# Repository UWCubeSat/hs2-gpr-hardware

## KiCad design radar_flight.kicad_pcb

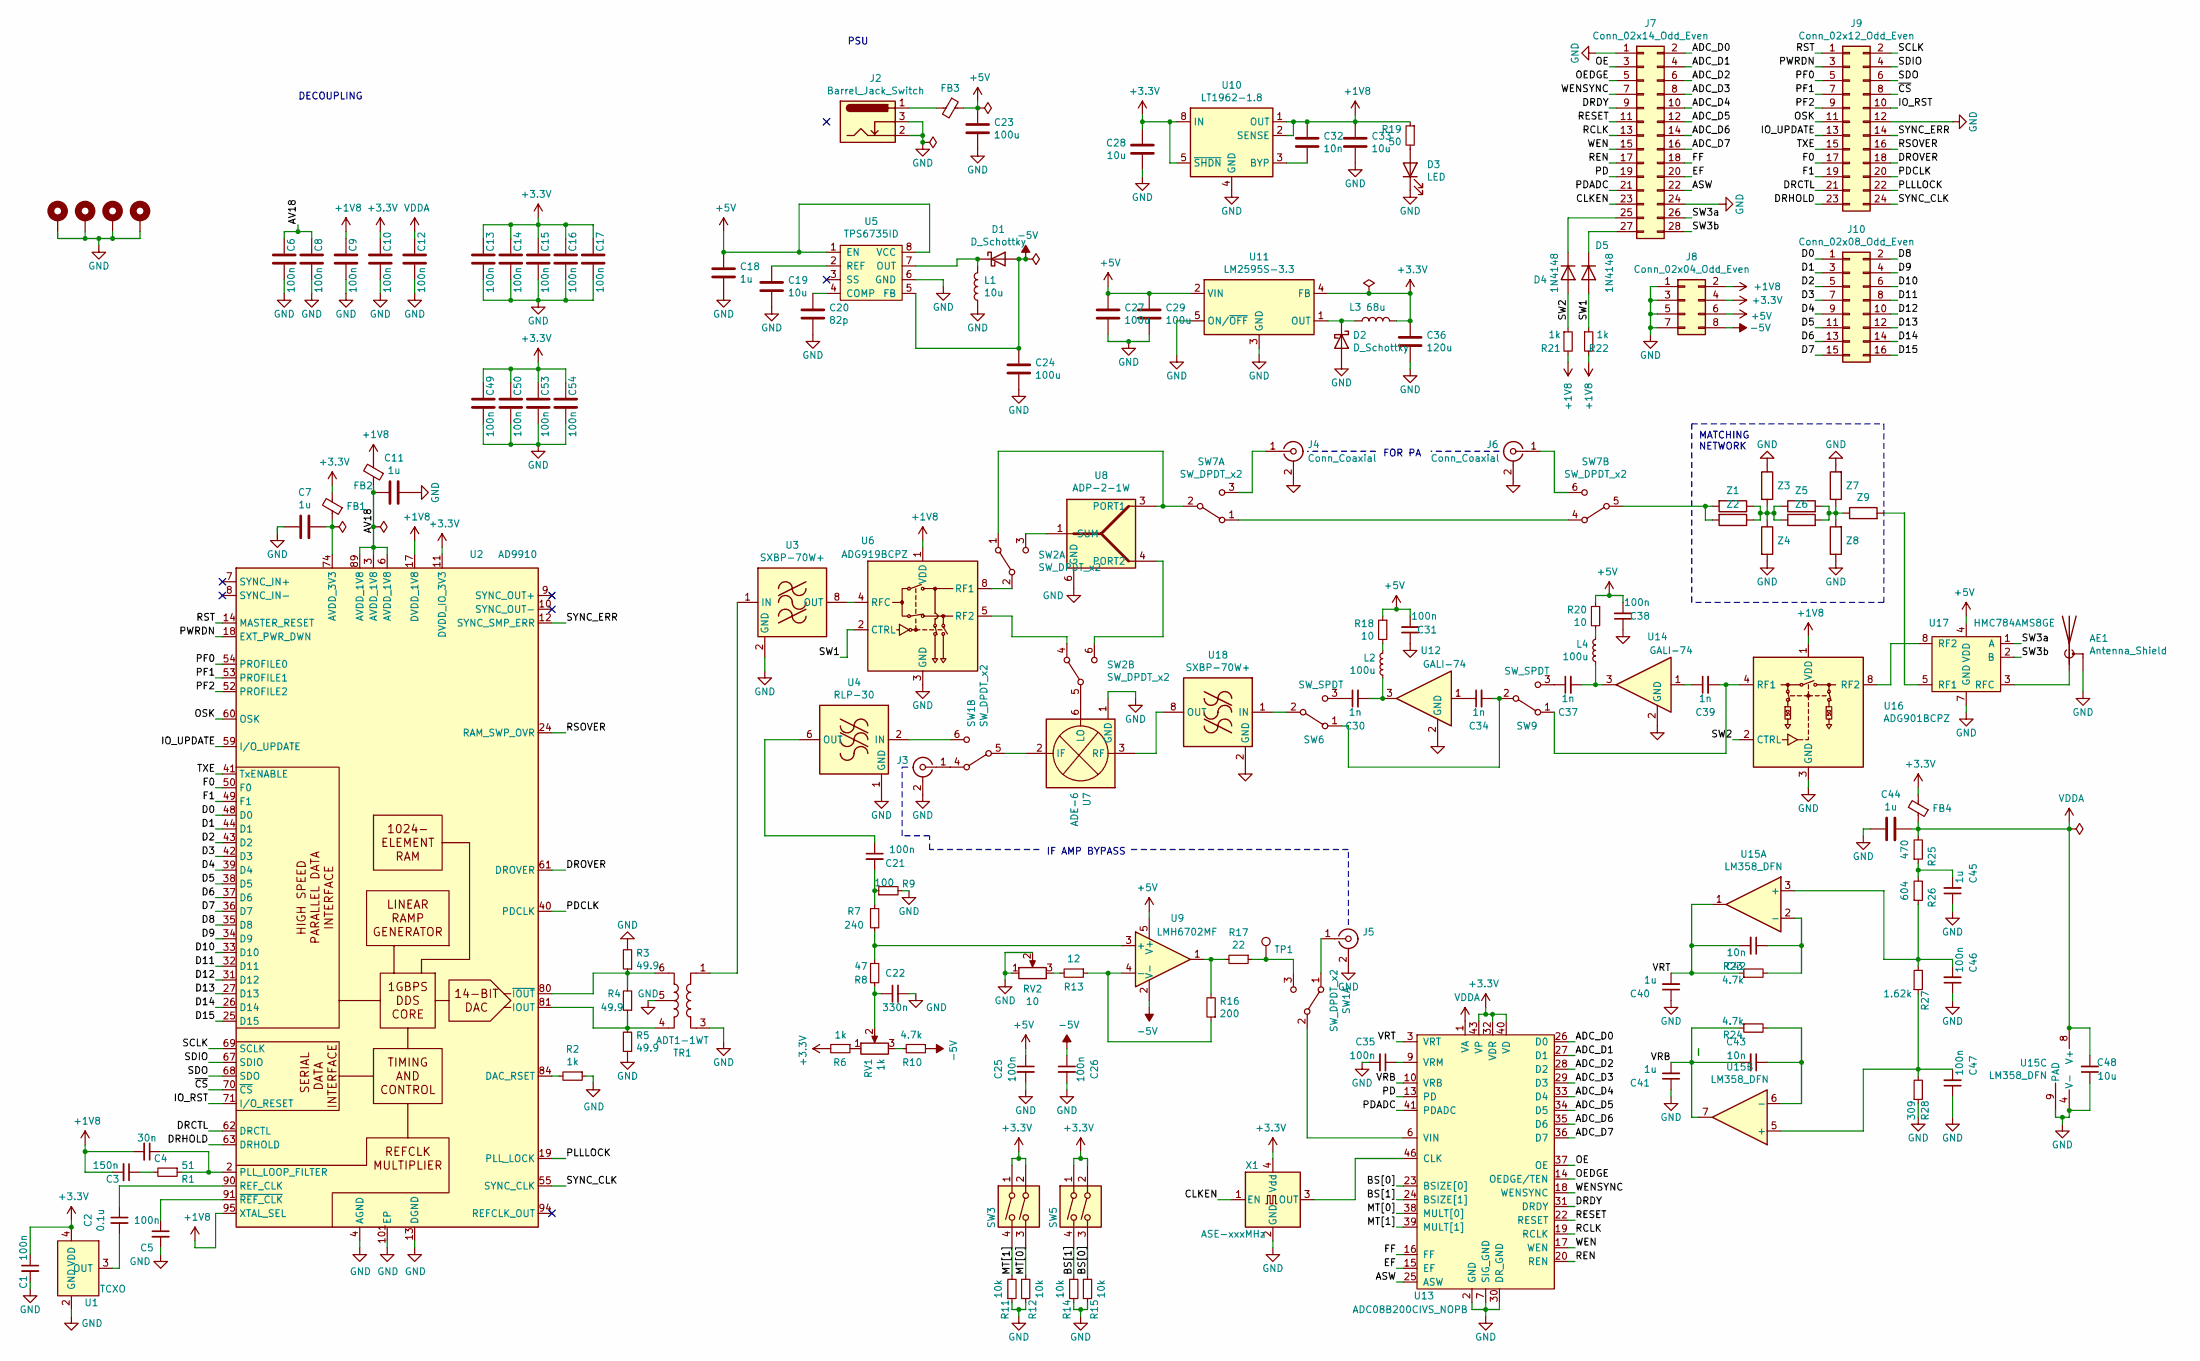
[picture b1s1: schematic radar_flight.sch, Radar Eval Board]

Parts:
AE1: Antenna_Shield; MMCX_Molex_73415-0961_Horizontal_0.8mm-PCB
C1, C5, C6, C8, C9, C10, C12, C13, C14, C15, C16, C17, C21, C25, C26, C31, C35, C38, C46, C47, C49, C50, C53, C54: 100n; C_0603_1608Metric
C2: 0.1u; C_0603_1608Metric
C3: 150n; C_0603_1608Metric
C4: 30n; C_0603_1608Metric
C7, C11, C18, C40, C41, C44, C45: 1u; C_0603_1608Metric
C19, C28, C33, C48: 10u; C_0603_1608Metric
C20: 82p; C_0603_1608Metric
C22: 330n; C_0603_1608Metric
C23, C24, C27, C29: 100u; C_1206_3216Metric
C30, C34, C37, C39: 1n; C_0603_1608Metric
C32, C42, C43: 10n; C_0603_1608Metric
C36: 120u; C_1206_3216Metric
D1, D2: D_Schottky; D_SMB
D3: LED; LED_0603_1608Metric
D4, D5: 1N4148; D_SOD-123
FB1, FB2, FB3, FB4: Ferrite_Bead_Small; L_0805_2012Metric
H1, H2, H3, H4: MountingHole_Pad; MountingHole_2.2mm_M2_Pad
J2: Barrel_Jack_Switch; BarrelJack_Wuerth_6941xx301002
J3, J4, J5, J6: Conn_Coaxial; SMA_Samtec_SMA-J-P-X-ST-EM1_EdgeMount
J7: Conn_02x14_Odd_Even; PinHeader_2x14_P2.54mm_Horizontal
J8: Conn_02x04_Odd_Even; PinHeader_2x04_P2.54mm_Horizontal
J9: Conn_02x12_Odd_Even; PinHeader_2x12_P2.54mm_Horizontal
J10: Conn_02x08_Odd_Even; PinHeader_2x08_P2.54mm_Horizontal
L1: 10u; L_Bourns-SRU8028_8.0x8.0mm
L2, L4: 100u; L_0805_2012Metric
L3: 68u; L_Bourns-SRU1028_10.0x10.0mm
R1: 51; R_0603_1608Metric
R2, R6, R21, R22: 1k; R_0603_1608Metric
R3, R4, R5: 49.9; R_0603_1608Metric
R7: 240; R_0603_1608Metric
R8: 47; R_0603_1608Metric
R9: 100; R_0603_1608Metric
R10, R23, R24: 4.7k; R_0603_1608Metric
R11, R12, R14, R15: 10k; R_0603_1608Metric
R13: 12; R_0603_1608Metric
R16: 200; R_0603_1608Metric
R17: 22; R_0603_1608Metric
R18, R20: 10; R_0603_1608Metric
R19: 50; R_0603_1608Metric
R25: 470; R_0603_1608Metric
R26: 604; R_0603_1608Metric
R27: 1.62k; R_0603_1608Metric
R28: 309; R_0603_1608Metric
RV1: 1k; Potentiometer_Bourns_3314J_Vertical
RV2: 10; Potentiometer_Bourns_3314J_Vertical
SW1, SW2, SW7: SW_DPDT_x2; SW_DPDT_CK_JS202011JCQN
SW3, SW5: SW_DIP_x02; SW_DIP_SPSTx02_Slide_Omron_A6S-210x_W8.9mm_P2.54mm
SW6, SW9: SW_SPDT; SW_SPDT_CK-JS102011SAQN
TP1: TestPoint; TestPoint_Pad_1.5x1.5mm
TR1: ADT1-1WT; Mini-Circuits_CD542_H2.84mm
U1: TCXO; FOX_5.0x3.2_SMD-4
U2: AD9910; TQFP-100-1EP_14x14mm_P0.5mm_EP5x5mm
U3, U18: SXBP-70W+; Mini-Circuits_HF1139_LandPatternPL-230
U4: RLP-30; Mini-Circuits_GP1212_LandPatternPL-176
U5: TPS6735ID; SOIC-8_3.9x4.9mm_P1.27mm
U6: ADG919BCPZ; LFCSP-8-1EP_3x3mm_P0.5mm_EP1.45x1.74mm
U7: ADE-6; Mini-Circuits_CD542_LandPatternPL-052
U8: ADP-2-1W; Mini-Circuits_CD636_LandPatternPL-035
U9: LMH6702MF; SOT-23-5
U10: LT1962-1.8; MSOP-8_3x3mm_P0.65mm
U11: LM2595S-3.3; TO-263-5_TabPin3
U12, U14: GALI-74; SOT-89-3
U13: ADC08B200CIVS_NOPB; TQFP-48_7x7mm_P0.5mm
U15: LM358_DFN; DFN-8-1EP_2x2mm_P0.5mm_EP1.05x1.75mm
U16: ADG901BCPZ; LFCSP-8-1EP_3x3mm_P0.5mm_EP1.45x1.74mm
U17: HMC784AMS8GE; MSOP-8-1EP_3x3mm_P0.65mm_EP1.95x2.15mm_ThermalVias
X1: ASE-xxxMHz; Oscillator_SMD_Abracon_ASE-4Pin_3.2x2.5mm
Z1, Z2, Z3, Z4, Z5, Z6, Z7, Z8, Z9: R_0805_2012Metric

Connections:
+1V8: C3.2, C4.2, C9.2, C32.2, C33.2, FB2.2, J8.2, R19.1, R21.2, R22.2, U2.17 (DVDD_1V8), U2.23 (DVDD_1V8), U2.30 (DVDD_1V8), U2.47 (DVDD_1V8), U2.57 (DVDD_1V8), U2.64 (DVDD_1V8), U2.95 (XTAL_SEL), U6.1 (VDD), U10.1 (OUT), U10.2 (SENSE), U16.1 (VDD)
+3V3: C1.1, C10.2, C13.2, C14.2, C15.2, C16.2, C17.2, C28.2, C36.2, C49.2, C50.2, C53.2, C54.2, FB1.2, FB4.2, J8.4, L3.2, R6.2, SW3.1, SW3.2, SW5.1, SW5.2, U1.4 (VDD), U2.11 (DVDD_IO_3V3), U2.15 (DVDD_IO_3V3), U2.21 (DVDD_IO_3V3), U2.28 (DVDD_IO_3V3), U2.45 (DVDD_IO_3V3), U2.56 (DVDD_IO_3V3), U2.66 (DVDD_IO_3V3), U10.5 (~SHDN), U10.8 (IN), U11.4 (FB), U13.32 (VDR), U13.40 (VD), U13.43 (VP), U13.44 (VP), U13.48 (VP), X1.4 (Vdd)
+5V: C18.2, C23.2, C25.1, C27.2, C29.2, C31.2, C38.2, FB3.1, J8.6, R18.1, R20.1, U5.1 (EN), U5.8 (VCC), U9.5 (V+), U11.2 (VIN), U17.4 (VDD)
-5V: C24.2, C26.1, D1.2 (A), J8.8, R10.1, U5.5 (FB), U9.2 (V-)
/ADC_D0: J7.2, U13.26 (D0)
/ADC_D1: J7.4, U13.27 (D1)
/ADC_D2: J7.6, U13.28 (D2)
/ADC_D3: J7.8, U13.29 (D3)
/ADC_D4: J7.10, U13.33 (D4)
/ADC_D5: J7.12, U13.34 (D5)
/ADC_D6: J7.14, U13.35 (D6)
/ADC_D7: J7.16, U13.36 (D7)
/ASW: J7.22, U13.25 (ASW)
/AV18: C6.2, C8.2, C11.1, FB2.1, U2.3 (AVDD_1V8), U2.6 (AVDD_1V8), U2.89 (AVDD_1V8), U2.92 (AVDD_1V8)
/BS[0]: R15.2, SW5.3, U13.23 (BSIZE[0])
/BS[1]: R14.2, SW5.4, U13.24 (BSIZE[1])
/CLKEN: J7.23, X1.1 (EN)
/D0: J10.1, U2.48 (D0)
/D1: J10.3, U2.44 (D1)
/D2: J10.5, U2.43 (D2)
/D3: J10.7, U2.42 (D3)
/D4: J10.9, U2.39 (D4)
/D5: J10.11, U2.38 (D5)
/D6: J10.13, U2.37 (D6)
/D7: J10.15, U2.36 (D7)
/D8: J10.2, U2.35 (D8)
/D9: J10.4, U2.34 (D9)
/D10: J10.6, U2.33 (D10)
/D11: J10.8, U2.32 (D11)
/D12: J10.10, U2.31 (D12)
/D13: J10.12, U2.27 (D13)
/D14: J10.14, U2.26 (D14)
/D15: J10.16, U2.25 (D15)
/DRCTL: J9.21, U2.62 (DRCTL)
/DRDY: J7.9, U13.31 (DRDY)
/DRHOLD: J9.23, U2.63 (DRHOLD)
/DROVER: J9.18, U2.61 (DROVER)
/EF: J7.20, U13.15 (EF)
/F0: J9.17, U2.50 (F0)
/F1: J9.19, U2.49 (F1)
/FF: J7.18, U13.16 (FF)
/IO_RST: J9.10, U2.71 (I/O_RESET)
/IO_UPDATE: J9.13, U2.59 (I/O_UPDATE)
/MT[0]: R12.2, SW3.3, U13.38 (MULT[0])
/MT[1]: R11.2, SW3.4, U13.39 (MULT[1])
/OE: J7.3, U13.37 (OE)
/OEDGE: J7.5, U13.14 (OEDGE/TEN)
/OSK: J9.11, U2.60 (OSK)
/PD: J7.19, U13.13 (PD)
/PDADC: J7.21, U13.41 (PDADC)
/PDCLK: J9.20, U2.40 (PDCLK)
/PF0: J9.5, U2.54 (PROFILE0)
/PF1: J9.7, U2.53 (PROFILE1)
/PF2: J9.9, U2.52 (PROFILE2)
/PLLLOCK: J9.22, U2.19 (PLL_LOCK)
/PWRDN: J9.3, U2.18 (EXT_PWR_DWN)
/RCLK: J7.13, U13.19 (RCLK)
/REN: J7.17, U13.20 (REN)
/RESET: J7.11, U13.22 (RESET)
/RSOVER: J9.16, U2.24 (RAM_SWP_OVR)
/RST: J9.1, U2.14 (MASTER_RESET)
/SCLK: J9.2, U2.69 (SCLK)
/SDIO: J9.4, U2.67 (SDIO)
/SDO: J9.6, U2.68 (SDO)
/SW1: D5.2 (A), R22.1, U6.2 (CTRL)
/SW2: D4.2 (A), R21.1, U16.2 (CTRL)
/SW3a: J7.26, U17.1 (A)
/SW3b: J7.28, U17.2 (B)
/SYNC_CLK: J9.24, U2.55 (SYNC_CLK)
/SYNC_ERR: J9.14, U2.12 (SYNC_SMP_ERR)
/TXE: J9.15, U2.41 (TxENABLE)
/VRB: C41.2, C43.2, R24.1, U13.10 (VRB), U15.7
/VRT: C40.2, C42.2, R23.1, U13.3 (VRT), U15.1
/WEN: J7.15, U13.17 (WEN)
/WENSYNC: J7.7, U13.18 (WENSYNC)
/~CS: J9.8, U2.70 (~CS)
GND: AE1.2 (Shield), C1.2, C5.2, C6.1, C7.1, C8.1, C9.1, C10.1, C11.2, C12.1, C13.1, C14.1, C15.1, C16.1, C17.1, C18.1, C19.1, C20.1, C22.2, C23.1, C24.1, C25.2, C26.2, C27.1, C28.1, C29.1, C31.1, C33.1, C35.2, C36.1, C38.1, C40.1, C41.1, C44.1, C45.1, C46.1, C47.1, C48.1, C49.1, C50.1, C53.1, C54.1, D2.2 (A), D3.1 (K), H1.1, H2.1, H3.1, H4.1, J2.2, J2.3, J3.2 (Ext), J4.2 (Ext), J5.2 (Ext), J6.2 (Ext), J7.1, J7.24, J8.1, J8.3, J8.5, J8.7, J9.12, L1.1, R2.1, R3.2, R5.1, R9.2, R11.1, R12.1, R14.1, R15.1, R28.1, RV2.1, RV2.2, TR1.3, TR1.5, U1.2 (GND), U2.4 (AGND), U2.5 (AGND), U2.13 (DGND), U2.16 (DGND), U2.22 (DGND), U2.29 (DGND), U2.46 (DGND), U2.51 (DGND), U2.58 (DGND), U2.65 (DGND), U2.73 (AGND), U2.78 (AGND), U2.79 (AGND), U2.82 (AGND), U2.85 (AGND), U2.88 (AGND), U2.96 (AGND), U2.101 (EP), U3.2 (GND), U3.3 (GND), U3.4 (GND), U3.5 (GND), U3.6 (GND), U3.7 (GND), U4.1 (GND), U4.3 (GND), U4.4 (GND), U4.5 (GND), U4.7 (GND), U4.8 (GND), U5.6 (GND), U6.3 (GND), U6.6 (GND), U6.7 (GND), U6.9 (GND), U7.1 (GND), U7.4 (GND), U7.5 (GND), U8.6 (GND), U10.4 (GND), U11.3 (GND), U11.5 (ON/~OFF), U12.2 (GND), U13.2 (GND), U13.5 (GND), U13.7 (SIG_GND), U13.8 (GND), U13.11 (GND), U13.21 (GND), U13.30 (DR_GND), U13.42 (GND), U13.45 (GND), U13.47 (GND), U14.2 (GND), U15.4 (V-), U15.9 (PAD), U16.3 (GND), U16.5 (GND), U16.6 (GND), U16.7 (GND), U16.9 (GND), U17.6 (GND), U17.7 (GND), U17.9 (GND), U18.2 (GND), U18.3 (GND), U18.4 (GND), U18.5 (GND), U18.6 (GND), U18.7 (GND), X1.2 (GND), Z3.1, Z4.2, Z7.2, Z8.1
unnamed: AE1.1 (A), U17.3 (RFC)
unnamed: C2.1, U2.90 (REF_CLK)
unnamed: C2.2, U1.3 (OUT)
unnamed: C3.1, R1.2
unnamed: C4.1, R1.1, U2.2 (PLL_LOOP_FILTER)
unnamed: C5.1, U2.91 (~REF_CLK)
unnamed: C7.2, FB1.1, U2.74 (AVDD_3V3), U2.75 (AVDD_3V3), U2.76 (AVDD_3V3), U2.77 (AVDD_3V3), U2.83 (AVDD_3V3)
unnamed: C19.2, U5.2 (REF)
unnamed: C20.2, U5.4 (COMP)
unnamed: C21.1, U4.6 (OUT)
unnamed: C21.2, R7.1, R9.1
unnamed: C22.1, R8.2, RV1.2
unnamed: C30.1, SW6.3 (C)
unnamed: C30.2, L2.2, U12.3
unnamed: C32.1, U10.3 (BYP)
unnamed: C34.1, U12.1
unnamed: C34.2, SW6.1 (A), SW9.2 (B)
unnamed: C35.1, U13.9 (VRM)
unnamed: C37.1, SW9.3 (C)
unnamed: C37.2, L4.2, U14.3
unnamed: C39.1, U14.1
unnamed: C39.2, SW9.1 (A), U16.4 (RF1)
unnamed: C42.1, R23.2, U15.2 (-)
unnamed: C43.1, R24.2, U15.6 (-)
unnamed: C45.2, R25.1, R26.2
unnamed: C46.2, R26.1, R27.2, U15.3 (+)
unnamed: C47.2, R27.1, R28.2, U15.5 (+)
unnamed: D1.1 (K), L1.2, U5.7 (OUT)
unnamed: D2.1 (K), L3.1, U11.1 (OUT)
unnamed: D3.2 (A), R19.2
unnamed: D4.1 (K), J7.25
unnamed: D5.1 (K), J7.27
unnamed: FB3.2, J2.1
unnamed: J3.1 (In), SW1.4 (A)
unnamed: J4.1 (In), SW7.3 (C)
unnamed: J5.1 (In), SW1.1 (A)
unnamed: J6.1 (In), SW7.6 (C)
unnamed: L2.1, R18.2
unnamed: L4.1, R20.2
unnamed: R2.2, U2.84 (DAC_RSET)
unnamed: R3.1, R4.2, TR1.6, U2.80 (~IOUT)
unnamed: R4.1, R5.2, TR1.4, U2.81 (IOUT)
unnamed: R6.1, RV1.1
unnamed: R7.2, R8.1, U9.3 (+)
unnamed: R10.2, RV1.3
unnamed: R13.1, R16.1, U9.4 (-)
unnamed: R13.2, RV2.3
unnamed: R16.2, R17.2, U9.1
unnamed: R17.1, SW1.3 (C), TP1.1
unnamed: SW1.2 (B), U13.6 (VIN)
unnamed: SW1.5 (B), U7.2 (IF)
unnamed: SW1.6 (C), U4.2 (IN)
unnamed: SW2.1 (A), SW7.2 (B), U8.3 (PORT1)
unnamed: SW2.2 (B), U6.8 (RF1)
unnamed: SW2.3 (C), U8.1 (SUM)
unnamed: SW2.4 (A), U6.5 (RF2)
unnamed: SW2.5 (B), U7.6 (LO)
unnamed: SW2.6 (C), U8.4 (PORT2)
unnamed: SW6.2 (B), U18.1 (IN)
unnamed: SW7.1 (A), SW7.4 (A)
unnamed: SW7.5 (B), Z1.2, Z2.2
unnamed: TR1.1, U3.1 (IN)
unnamed: U3.8 (OUT), U6.4 (RFC)
unnamed: U13.46 (CLK), X1.3 (OUT)
unnamed: U16.8 (RF2), U17.8 (RF2)
unnamed: U17.5 (RF1), Z9.2
unnamed: U7.3 (RF), U18.8 (OUT)
unnamed: Z1.1, Z2.1, Z3.2, Z4.1, Z5.1, Z6.1
unnamed: Z5.2, Z6.2, Z7.1, Z8.2, Z9.1
VA: C12.2, C44.2, C48.2, FB4.1, R25.2, U13.1 (VA), U13.4 (VA), U13.12 (VA), U15.8 (V+)

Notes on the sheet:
MATCHING NETWORK
FOR PA
PSU
IF AMP BYPASS
DECOUPLING

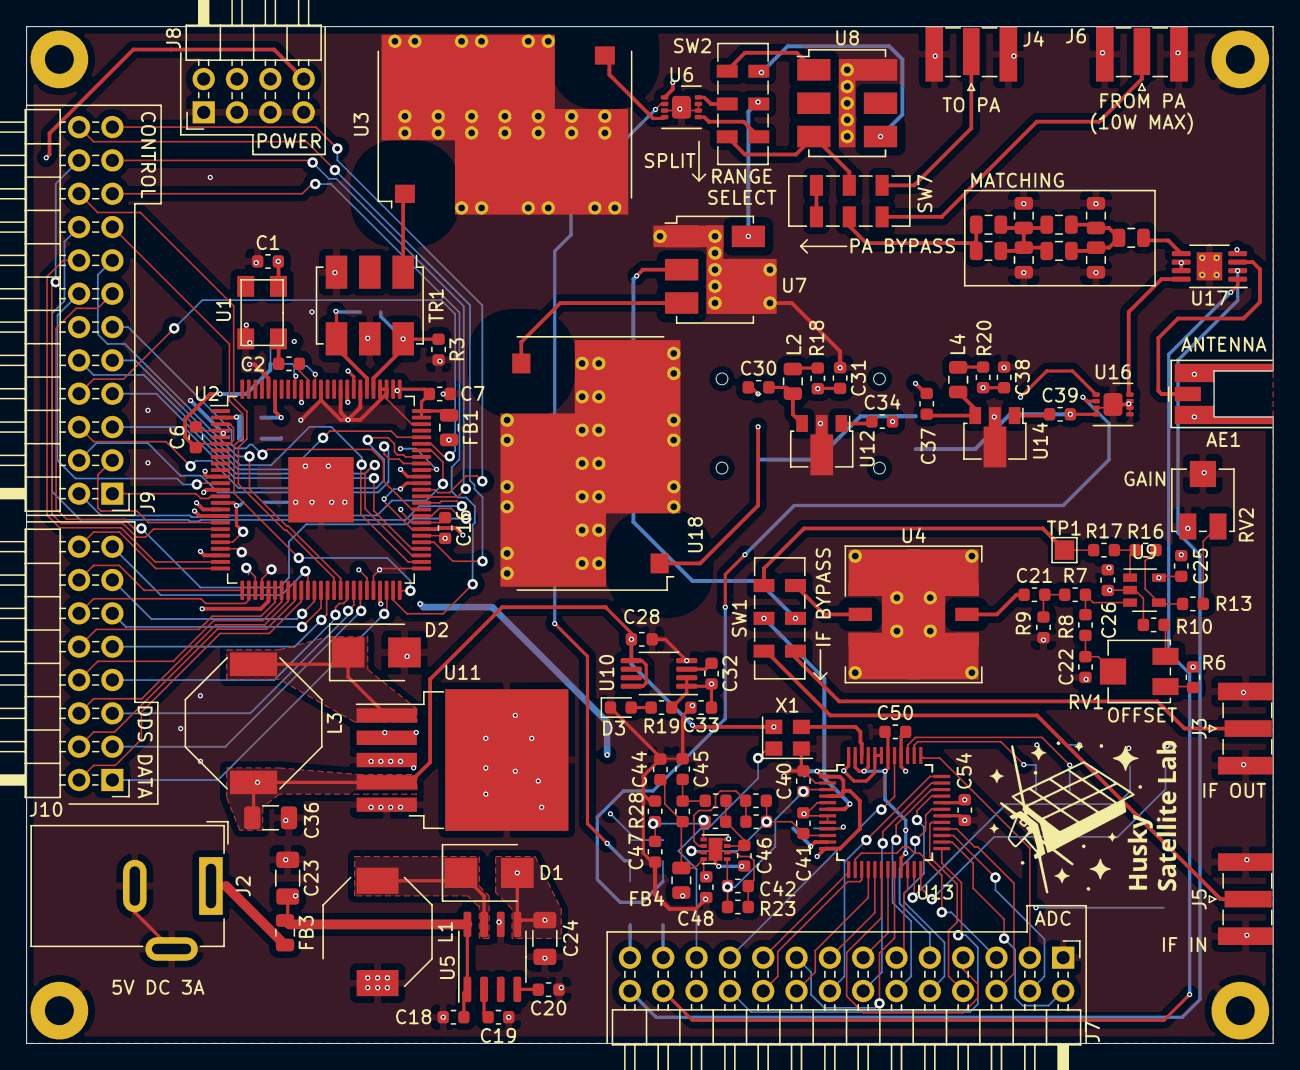
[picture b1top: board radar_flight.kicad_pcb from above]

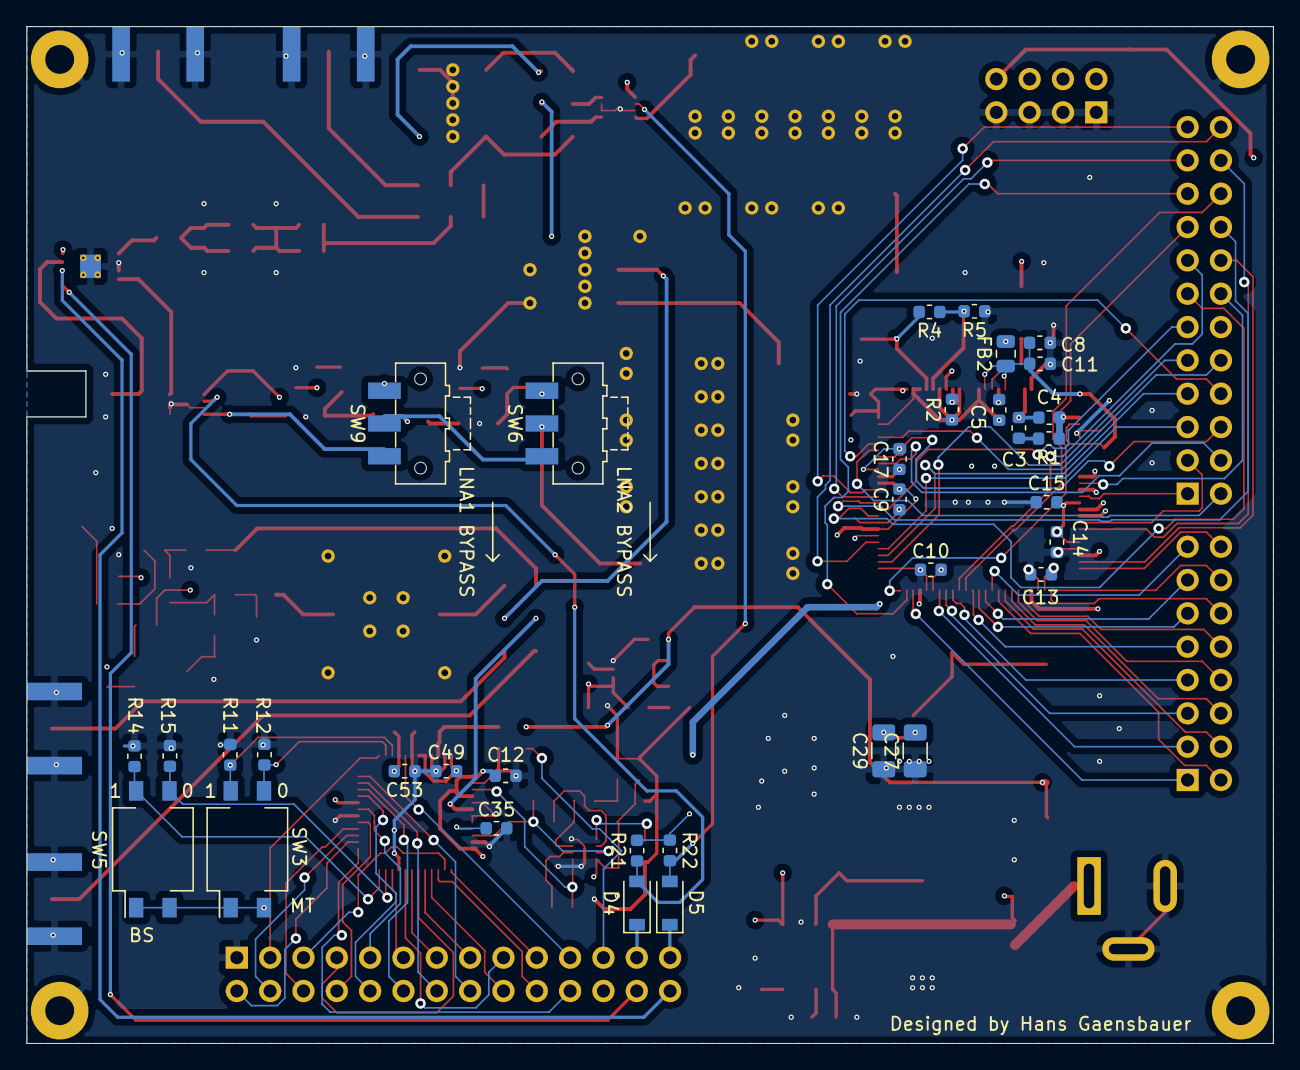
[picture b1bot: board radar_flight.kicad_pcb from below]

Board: 4 copper layers, 95.0 x 77.5 mm, 146 parts (34 on the bottom side), 147 nets.

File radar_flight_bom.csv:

Reference, Quantity, Value, Footprint, Datasheet
AE1 ,1,"Antenna_Shield","Connector_Coaxial:MMCX_Molex_73415-0961_Horizontal_0.8mm-PCB","~"
C2 C5 C1 ,3,"0.1u","Capacitor_SMD:C_0603_1608Metric","~"
C20 ,1,"82p","Capacitor_SMD:C_0603_1608Metric","~"
C22 ,1,"330n","Capacitor_SMD:C_0603_1608Metric","~"
C24 C29 C27 C23 ,4,"100u","Capacitor_SMD:C_1206_3216Metric","~"
C3 ,1,"0.15u","Capacitor_SMD:C_0603_1608Metric","~"
C36 ,1,"120u","Capacitor_SMD:C_1206_3216Metric","~"
C37 C39 C30 C34 ,4,"1n","Capacitor_SMD:C_0603_1608Metric","~"
C38 C31 C47 C46 C35 C25 C26 C21 C6 C8 C9 C10 C12 C13 C14 C15 C16 C17 C50 C53 C54 C49 ,22,"100n","Capacitor_SMD:C_0603_1608Metric","~"
C4 ,1,"30n","Capacitor_SMD:C_0603_1608Metric","~"
C43 C42 C32 ,3,"10n","Capacitor_SMD:C_0603_1608Metric","~"
C45 C41 C18 C7 C44 C11 C40 ,7,"1u","Capacitor_SMD:C_0603_1608Metric","~"
C48 C19 C33 C28 ,4,"10u","Capacitor_SMD:C_0603_1608Metric","~"
D2 D1 ,2,"D_Schottky","Diode_SMD:D_SMB","~"
D3 ,1,"LED","LED_SMD:LED_0603_1608Metric","~"
D5 D4 ,2,"1N4148","Diode_SMD:D_SOD-123","https://assets.nexperia.com/documents/data-sheet/1N4148_1N4448.pdf"
FB3 FB1 FB4 FB2 ,4,"Ferrite_Bead_Small","Inductor_SMD:L_0805_2012Metric","~"
H1 H2 H3 H4 ,4,"MountingHole_Pad","MountingHole:MountingHole_2.2mm_M2_Pad","~"
J10 ,1,"Conn_02x08_Odd_Even","Connector_PinHeader_2.54mm:PinHeader_2x08_P2.54mm_Horizontal","~"
J2 ,1,"Barrel_Jack_Switch","Connector_BarrelJack:BarrelJack_Wuerth_6941xx301002","~"
J4 J6 J3 J5 ,4,"Conn_Coaxial","Connector_Coaxial:SMA_Samtec_SMA-J-P-X-ST-EM1_EdgeMount"," ~"
J7 ,1,"Conn_02x14_Odd_Even","Connector_PinHeader_2.54mm:PinHeader_2x14_P2.54mm_Horizontal","~"
J8 ,1,"Conn_02x04_Odd_Even","Connector_PinHeader_2.54mm:PinHeader_2x04_P2.54mm_Horizontal","~"
J9 ,1,"Conn_02x12_Odd_Even","Connector_PinHeader_2.54mm:PinHeader_2x12_P2.54mm_Horizontal","~"
L1 ,1,"10u","Inductor_SMD:L_Bourns-SRU8028_8.0x8.0mm","~"
L3 ,1,"68u","Inductor_SMD:L_Bourns-SRU1028_10.0x10.0mm","~"
L4 L2 ,2,"100u","Inductor_SMD:L_0805_2012Metric","~"
R1 ,1,"51","Resistor_SMD:R_0603_1608Metric","~"
R13 ,1,"12","Resistor_SMD:R_0603_1608Metric","~"
R15 R14 R12 R11 ,4,"10k","Resistor_SMD:R_0603_1608Metric","~"
R16 ,1,"200","Resistor_SMD:R_0603_1608Metric","~"
R17 ,1,"22","Resistor_SMD:R_0603_1608Metric","~"
R19 ,1,"50","Resistor_SMD:R_0603_1608Metric","~"
R2 R6 R22 R21 ,4,"1k","Resistor_SMD:R_0603_1608Metric","~"
R20 R18 ,2,"10","Resistor_SMD:R_0603_1608Metric","~"
R24 R23 R10 ,3,"4.7k","Resistor_SMD:R_0603_1608Metric","~"
R25 ,1,"470","Resistor_SMD:R_0603_1608Metric","~"
R26 ,1,"604","Resistor_SMD:R_0603_1608Metric","~"
R27 ,1,"1.62k","Resistor_SMD:R_0603_1608Metric","~"
R28 ,1,"309","Resistor_SMD:R_0603_1608Metric","~"
R5 R3 R4 ,3,"49.9","Resistor_SMD:R_0603_1608Metric","~"
R7 ,1,"240","Resistor_SMD:R_0603_1608Metric","~"
R8 ,1,"47","Resistor_SMD:R_0603_1608Metric","~"
R9 ,1,"100","Resistor_SMD:R_0603_1608Metric","~"
RV1 ,1,"1k","Potentiometer_SMD:Potentiometer_Bourns_3314J_Vertical","~"
RV2 ,1,"10","Potentiometer_SMD:Potentiometer_Bourns_3314J_Vertical","~"
SW5 SW3 ,2,"SW_DIP_x02","Button_Switch_SMD:SW_DIP_SPSTx02_Slide_Omron_A6S-210x_W8.9mm_P2.54mm","~"
SW7 SW2 SW1 ,3,"SW_DPDT_x2","Button_Switch_SMD:SW_DPDT_CK_JS202011JCQN",""
SW9 SW6 ,2,"SW_SPDT","Button_Switch_SMD:SW_SPDT_CK-JS102011SAQN","~"
TP1 ,1,"TestPoint","TestPoint:TestPoint_Pad_1.5x1.5mm","~"
TR1 ,1,"ADT1-1WT","RF_Mini-Circuits:Mini-Circuits_CD542_H2.84mm","https://www.minicircuits.com/pdfs/ADT1-1WT+.pdf"
U1 ,1,"TCXO","HS2_parts:FOX_5.0x3.2_SMD-4",""
U10 ,1,"LT1962-1.8","Package_SO:MSOP-8_3x3mm_P0.65mm","https://www.analog.com/media/en/technical-documentation/data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"
U11 ,1,"LM2595S-3.3","Package_TO_SOT_SMD:TO-263-5_TabPin3","http://www.ti.com.cn/cn/lit/ds/symlink/lm2595.pdf"
U13 ,1,"ADC08B200CIVS_NOPB","Package_QFP:TQFP-48_7x7mm_P0.5mm","https://www.digikey.com/en/products/detail/texas-instruments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"
U14 U12 ,2,"GALI-74","Package_TO_SOT_SMD:SOT-89-3","https://www.minicircuits.com/pdfs/GALI-74+.pdf"
U15 ,1,"LM358_DFN","Package_DFN_QFN:DFN-8-1EP_2x2mm_P0.5mm_EP1.05x1.75mm","www.st.com/resource/en/datasheet/lm358.pdf"
U16 ,1,"ADG901BCPZ","Package_CSP:LFCSP-8-1EP_3x3mm_P0.5mm_EP1.45x1.74mm","https://www.analog.com/media/en/technical-documentation/data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"
U17 ,1,"HMC784AMS8GE","Package_SO:MSOP-8-1EP_3x3mm_P0.65mm_EP1.95x2.15mm_ThermalVias","https://www.analog.com/media/en/technical-documentation/data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"
U2 ,1,"AD9910","Package_QFP:TQFP-100-1EP_14x14mm_P0.5mm_EP5x5mm","https://www.analog.com/media/en/technical-documentation/data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"
U3 U18 ,2,"SXBP-70W+","RF_Mini-Circuits:Mini-Circuits_HF1139_LandPatternPL-230","https://www.minicircuits.com/pdfs/SXBP-27R5+.pdf"
U4 ,1,"RLP-30","RF_Mini-Circuits:Mini-Circuits_GP1212_LandPatternPL-176","https://www.minicircuits.com/pdfs/RLP-30+.pdf"
U5 ,1,"TPS6735ID","Package_SO:SOIC-8_3.9x4.9mm_P1.27mm","https://www.ti.com/lit/ds/symlink/tps6735.pdf"
U6 ,1,"ADG919BCPZ","Package_CSP:LFCSP-8-1EP_3x3mm_P0.5mm_EP1.45x1.74mm","https://www.analog.com/media/en/technical-documentation/data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"
U7 ,1,"ADE-6","RF_Mini-Circuits:Mini-Circuits_CD542_LandPatternPL-052","www.minicircuits.com/pdfs/ADE-6.pdf"
U8 ,1,"ADP-2-1W","RF_Mini-Circuits:Mini-Circuits_CD636_LandPatternPL-035","https://www.minicircuits.com/pdfs/ADP-2-1W.pdf"
U9 ,1,"LMH6702MF","Package_TO_SOT_SMD:SOT-23-5","http://www.ti.com/lit/ds/symlink/lmh6702.pdf"
X1 ,1,"ASE-xxxMHz","Oscillator:Oscillator_SMD_Abracon_ASE-4Pin_3.2x2.5mm","http://www.abracon.com/Oscillators/ASV.pdf"
Z8 Z9 Z7 Z5 Z6 Z4 Z3 Z1 Z2 ,9,"~","Resistor_SMD:R_0805_2012Metric","~"

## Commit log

2021-05-08 Final radar
